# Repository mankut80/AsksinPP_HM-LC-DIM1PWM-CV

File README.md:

# AsksinPP_HM-LC-DIM1PWM-CV
12V PWM-Dimmer auf AsksinPP-Basis

eine modifizierte Version des 7-24V-Dimmers von psi (Danke dafür :-)).

Die große Neuerung hier ist der MOSFET-Treiber MIC4422. Wärmeverluste gehören damit der Vergangenheit an, der MOSFET bleibt lauwarm bis kalt. Der Nachteil ist die Tatsache, dass man um eine geätzte Platine nicht herumkommt. Schuld trägt besagter Treiber in der SMD-Variante.

Der zu verwendende MOSFET ist fast egal, Hauptsache er ist vom Typ "N-Kanal". Ein möglichst niedriger Rds-On-Wert (Durchlasswiderstand im eingeschalteten Zustand) ist wünschenswert. 
Ein typischer N-Kanal-MOSFET alter Bauart ist der BUZ11 mit einem Rds von 0,04 Ohm. 
Bei ihm beträgt der Leistungsverlust bei 6A: 6x6x0,04=1.5W. Das ist immer noch ohne Kühlkörper machbar. Besser ist natürlich der IRLB3036 mit einem Rds von 2,4mOhm, da kommt als Wärmeleistung 90mW heraus. Das ist quasi nichts. Die Umschaltverluste kommen da noch oben drauf, die sind aber vernachlässigbar.

Vorsicht!
Die höchste, zulässige Eingangsspannung ist 18V. 24V-LED-Bänder scheiden damit leider aus.

### Gehäuse
Das Gehäuse wird mit einer einzigen Schraube verschlossen. Im CAD-Verzeichnis liegen die passenden step-Dateien und das Original im FreeCAD-Format.

### Sketch
Im Sketch müssen die üblichen Anpassungen der Serial usw. vorgenommen werden. Ansonsten enspricht es genau der Version von psi.

### Bauteilliste
| Pos | Ref | Wert |
|-----|-----|------|
| 1 | C3, C4 | 100nF / Keramikkondensator, RM2.5 |
| 2 | C1 | 100µF / 25V D=6mm |
| 3	|	C2 | 100nF	C_Rect_L4.6mm_W3.0mm_P2.50mm_MKS02_FKP02 |
| 4	|	R1 | 330R, 0207 |
| 5	|	D1 | LED	3mm, Farbe egal |
| 6 |	U1 | L78L05, TO92 |
| 7	|	U2 | CC1101-Modul |
| 8 | U3 | MIC4422YM	SOIC-8 |
| 9 |	X1, X2 | Schraubklemme 2pol P5.00mm oder 5.08mm	|
| 10 | SW1 | Taster 6x6mm H5mm |
| 11 | SW2 | Taster 6x6mmm H5mm |
| 12 | A1	| Arduino Pro_Mini |
| 13 | Q1	| IRF3708 oder anderer N-Kanal MOSFET, TO-220 |
| 14 | J3	| AVR-ISP-6	Molex_PicoBlade_53047-0610_1x06_P1.25mm_Vertical |

Position 14 kann bedenkenlos weggelassen werden wenn man nicht per ISP programmieren möchte

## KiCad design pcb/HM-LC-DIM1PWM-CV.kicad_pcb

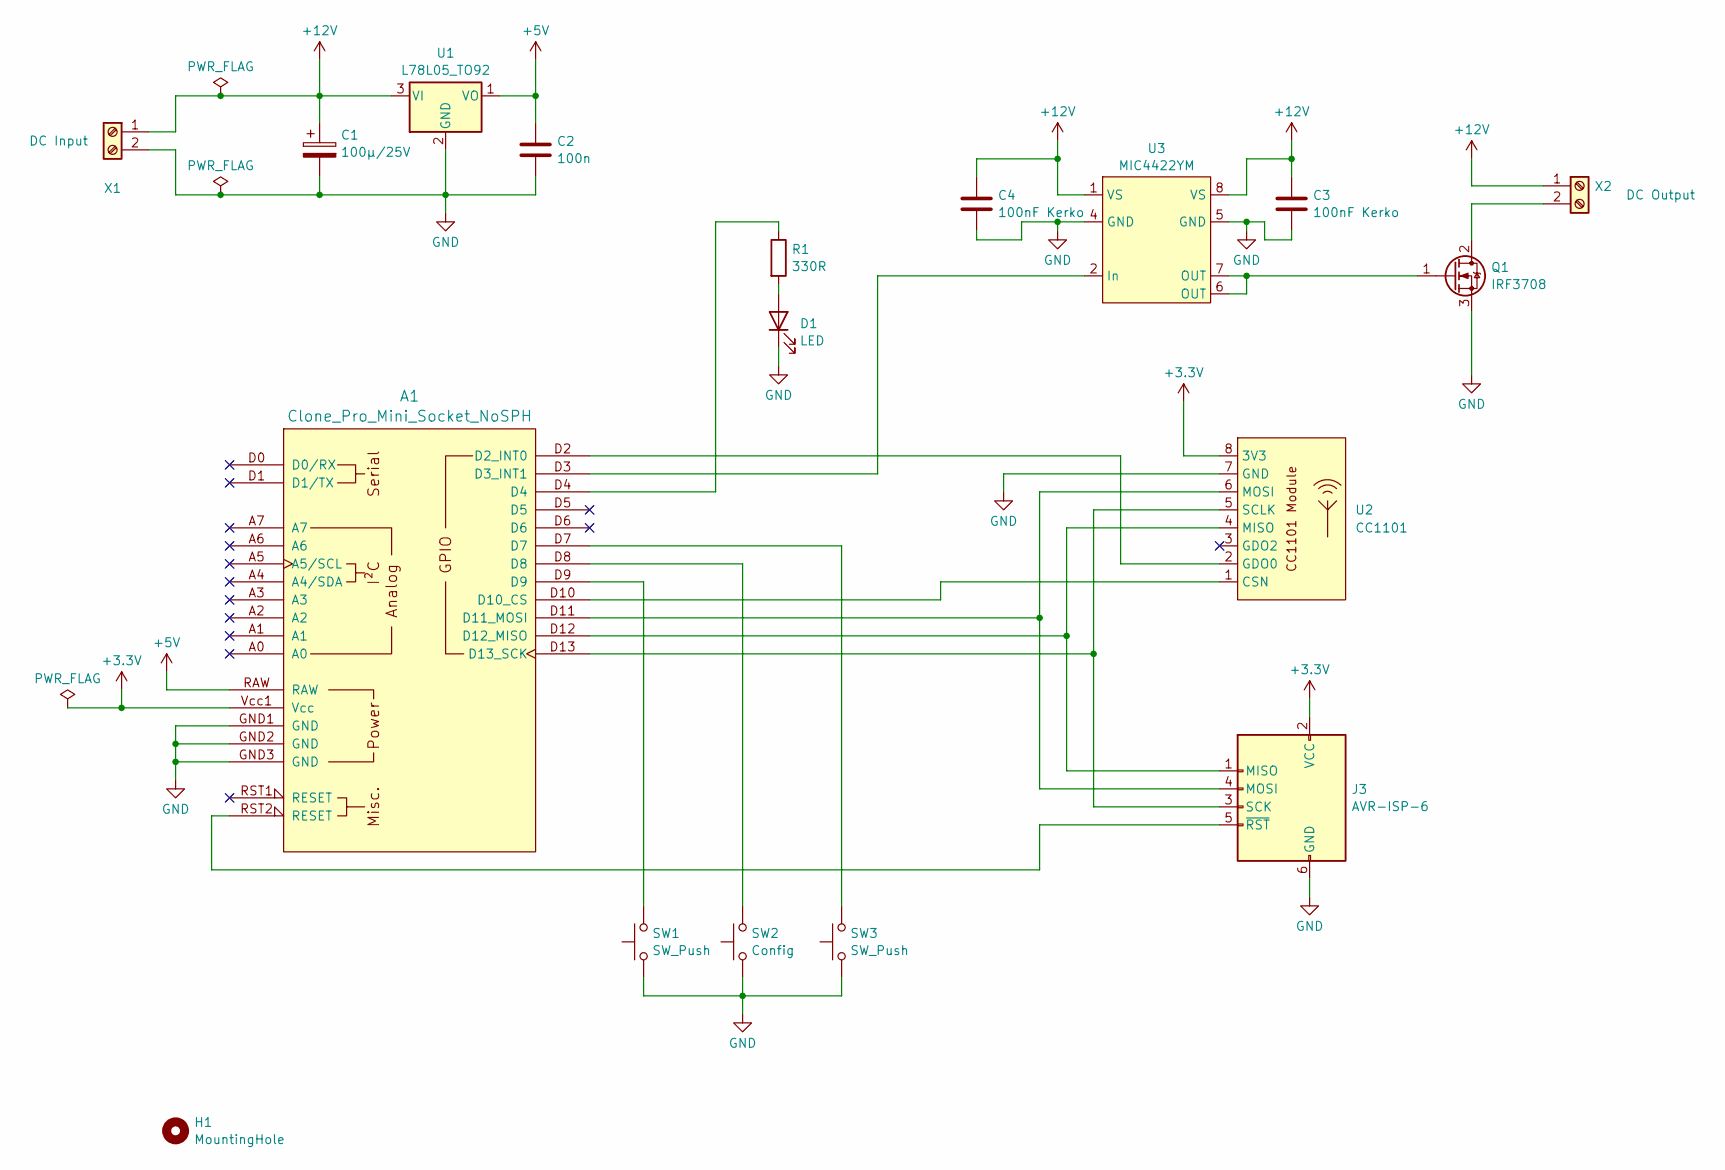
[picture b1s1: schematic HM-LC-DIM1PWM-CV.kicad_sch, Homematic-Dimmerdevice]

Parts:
A1: Clone_Pro_Mini_Socket_NoSPH
C1: 100µ/25V; CP_Radial_Tantal_D6.0mm_P2.50mm
C2: 100n; C_Rect_L4.6mm_W3.0mm_P2.50mm_MKS02_FKP02
C3, C4: 100nF Kerko; C_Disc_D3.0mm_W2.0mm_P2.50mm
D1: LED; LED_D3.0mm
H1: MountingHole; MountingHole_3.2mm_M3
J3: AVR-ISP-6; Molex_PicoBlade_53047-0610_1x06_P1.25mm_Vertical
Q1: IRF3708; TO-220-3_Vertical
R1: 330R; R_Axial_DIN0207_L6.3mm_D2.5mm_P2.54mm_Vertical
SW1, SW3: SW_Push; SW_PUSH_6mm_H5mm
SW2: Config; SW_PUSH_6mm_H5mm
U1: L78L05_TO92; TO-92_Inline
U2: CC1101; CC1101_Module_v1
U3: MIC4422YM; SOIC-8_3.9x4.9mm_P1.27mm
X1, X2: Screw_Terminal_01x02; TerminalBlock_Altech_AK300-2_P5.00mm

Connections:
+3.3V: A1.Vcc1 (Vcc), J3.2 (VCC), U2.8 (3V3)
+5V: A1.RAW, C2.1, U1.1 (VO)
+12V: C1.1, C3.1, C4.1, U1.3 (VI), U3.1 (VS), U3.8 (VS), X1.1, X2.1
GND: A1.GND1 (GND), A1.GND2 (GND), A1.GND3 (GND), C1.2, C2.2, C3.2, C4.2, D1.1 (K), J3.6 (GND), Q1.3 (S), SW1.1, SW2.1, SW3.1, U1.2 (GND), U2.7 (GND), U3.4 (GND), U3.5 (GND), X1.2
unnamed: A1.D2 (D2_INT0), U2.2 (GDO0)
unnamed: A1.D3 (D3_INT1), U3.2 (In)
unnamed: A1.D10 (D10_CS), U2.1 (CSN)
unnamed: A1.D11 (D11_MOSI), J3.4 (MOSI), U2.6 (MOSI)
unnamed: A1.D12 (D12_MISO), J3.1 (MISO), U2.4 (MISO)
unnamed: A1.D13 (D13_SCK), J3.3 (SCK), U2.5 (SCLK)
unnamed: A1.D4, R1.1
unnamed: A1.D7, SW3.2
unnamed: A1.D8, SW2.2
unnamed: A1.D9, SW1.2
unnamed: D1.2 (A), R1.2
unnamed: A1.RST2 (RESET), J3.5 (~RST)
unnamed: Q1.2 (D), X2.2
unnamed: Q1.1 (G), U3.6 (OUT), U3.7 (OUT)

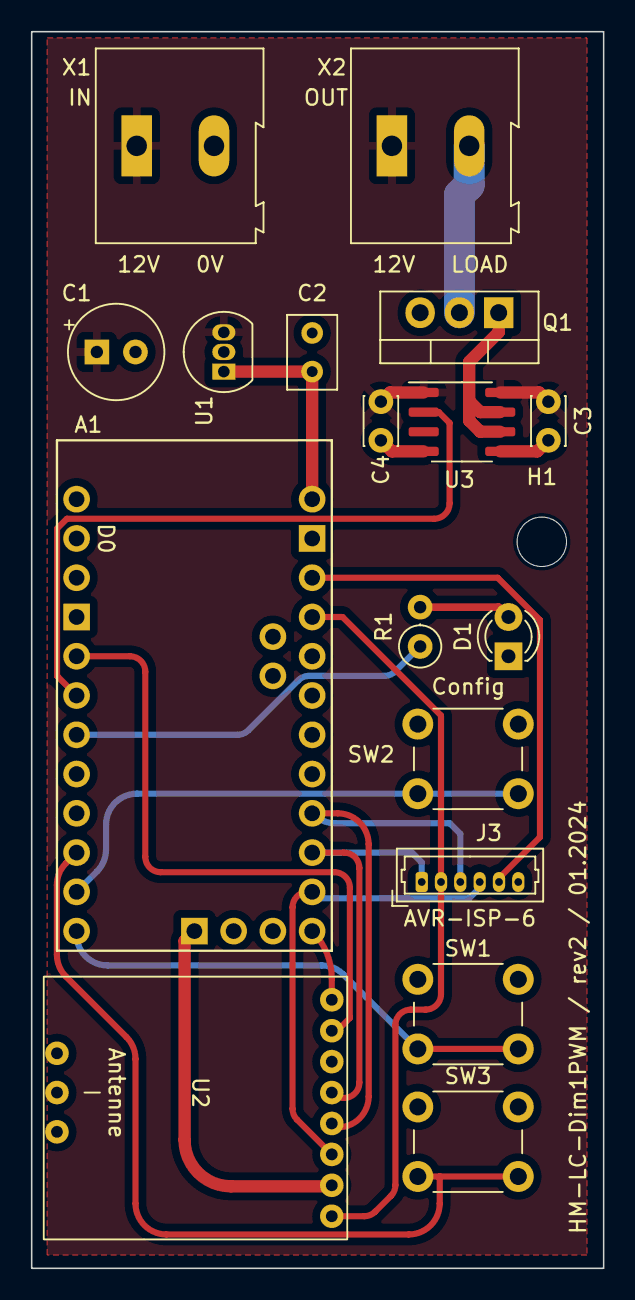
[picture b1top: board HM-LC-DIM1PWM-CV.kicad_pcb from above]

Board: 2 copper layers, 37.0 x 80.0 mm, 18 parts (0 on the bottom side), 18 nets.
